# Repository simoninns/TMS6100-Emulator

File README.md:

## Synopsis

TMS6100 speech PHROM (PHrase Read Only Memory) hardware emulator for use with the TMS5220 Voice Synthesis Processor in an Acorn BBC Microcomputer

## Motivation

This project creates a TMS6100 speech PHROM (PHrase Read Only Memory) for use with the TMS5220 Voice Synthesis Processor in an Acorn BBC Microcomputer. Whilst it’s still possible to purchase TMS5220 ICs from sites like Ebay, the TMS6100 was a mask-programmed ROM that Acorn produced specifically for their speech upgrade and is therefore difficult and expensive to source. Instead of using the original ROM, this project uses an ATmega32U2 microcontroller to both emulate the ROM and provide the original Acorn voice sample data recorded by BBC newsreader Kenneth Kendall.

## Installation

Note: This is an Atmel Studio 7 project that can be loaded and compiled by the IDE

Please see http://www.waitingforfriday.com/?p=30 for detailed documentation about TMS6100-Emulator

The PHROM data for both the Acorn Speech System PHROM and the American TI PHROM is included in the source-code.  By default it will compile using the Acorn Speech Data.  Specifying the compiler macro PHROM_ACORN selects the Acorn PHROM and PHROM_US selects the American PHROM.  Note that the American PHROM is not generally for use with the BBC Micro and is included for experimental use (or use in other microcomputer systems).

## Author

TMS6100-Emulator is written and maintained by Simon Inns.

## License (Software)

    TMS6100-Emulator is free software: you can redistribute it and/or modify
    it under the terms of the GNU General Public License as published by
    the Free Software Foundation, either version 3 of the License, or
    (at your option) any later version.

    TMS6100-Emulator is distributed in the hope that it will be useful,
    but WITHOUT ANY WARRANTY; without even the implied warranty of
    MERCHANTABILITY or FITNESS FOR A PARTICULAR PURPOSE.  See the
    GNU General Public License for more details.

    You should have received a copy of the GNU General Public License
    along with TMS6100-Emulator. If not, see <http://www.gnu.org/licenses/>.

## License (Hardware)

Both the schematic and the PCB design of TMS6100-Emulator are covered by a Creative Commons license; as with the software you are welcome (and encouraged!) to extend, re-spin and otherwise use and modify the design as allowed by the license.  However; under the terms of the Attribution-ShareAlike 4.0 International (CC BY-SA 4.0) license you are required to release your design (or redesign) under the same license.  For details of the licensing requirements please see <https://creativecommons.org/licenses/by-sa/4.0/>

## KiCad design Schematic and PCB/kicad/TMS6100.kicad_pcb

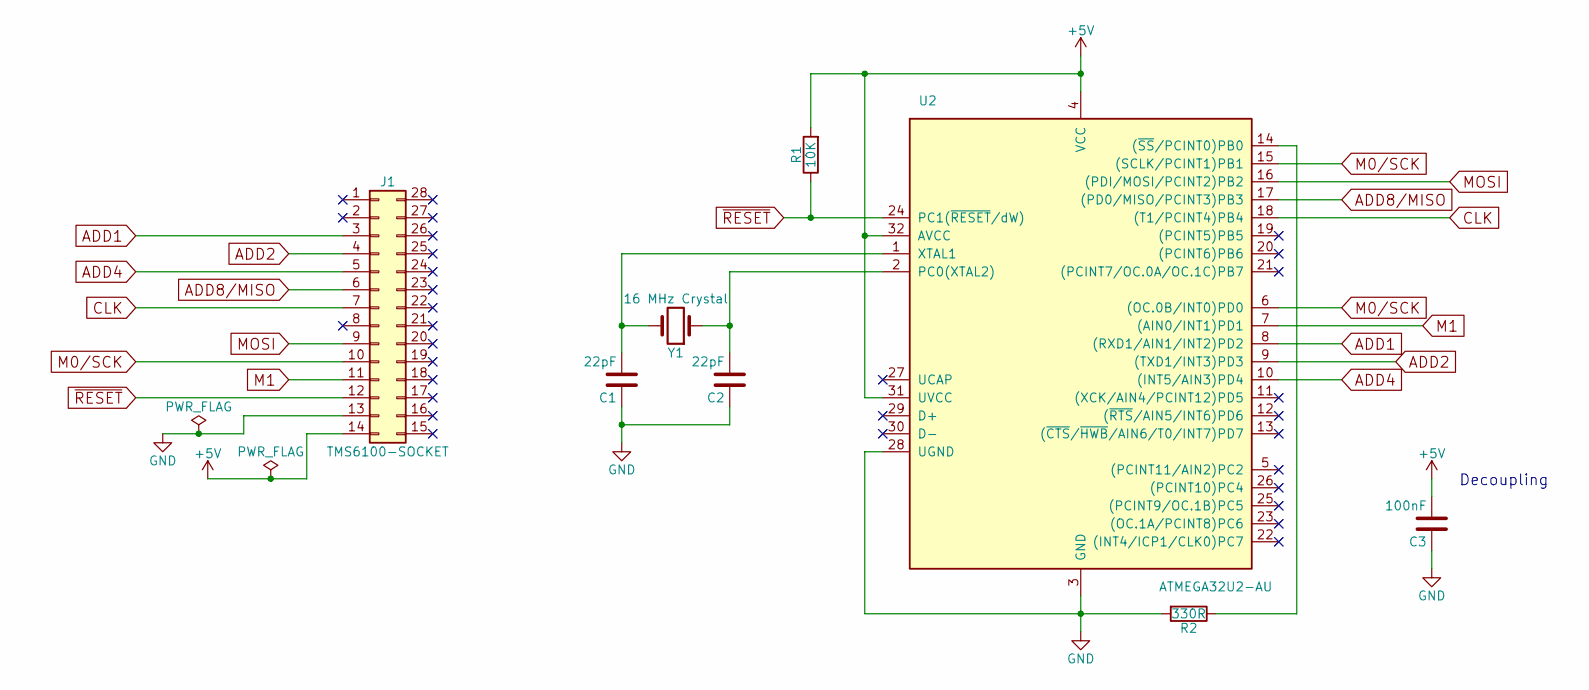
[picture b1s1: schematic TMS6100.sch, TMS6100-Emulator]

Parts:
C1, C2: 22pF; C_0805
C3: 100nF; C_0805
J1: TMS6100-SOCKET; DIP-28_W15.24mm_Socket
R1: 10K; R_0805
R2: 330R; R_0805
U2: ATMEGA32U2-AU; TQFP-32_7x7mm_Pitch0.8mm
Y1: 16 MHz Crystal; Crystal_SMD_5032-2pin_5.0x3.2mm

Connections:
+5V: C3.2, J1.14, R1.2, U2.4 (VCC), U2.31 (UVCC), U2.32 (AVCC)
ADD1: J1.3, U2.8 ((RXD1/AIN1/INT2)PD2)
ADD2: J1.4, U2.9 ((TXD1/INT3)PD3)
ADD4: J1.5, U2.10 ((INT5/AIN3)PD4)
ADD8/MISO: J1.6, U2.17 ((PD0/MISO/PCINT3)PB3)
CLK: J1.7, U2.18 ((T1/PCINT4)PB4)
GND: C1.1, C2.1, C3.1, J1.13, R2.2, U2.3 (GND), U2.28 (UGND)
M0/SCK: J1.10, U2.6 ((OC.0B/INT0)PD0), U2.15 ((SCLK/PCINT1)PB1)
M1: J1.11, U2.7 ((AIN0/INT1)PD1)
MOSI: J1.9, U2.16 ((PDI/MOSI/PCINT2)PB2)
unnamed: C1.2, U2.1 (XTAL1), Y1.2
unnamed: C2.2, U2.2 (PC0(XTAL2)), Y1.1
unnamed: R2.1, U2.14 ((~SS~/PCINT0)PB0)
~RESET: J1.12, R1.1, U2.24 (PC1(~RESET~/dW))

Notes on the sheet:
Decoupling

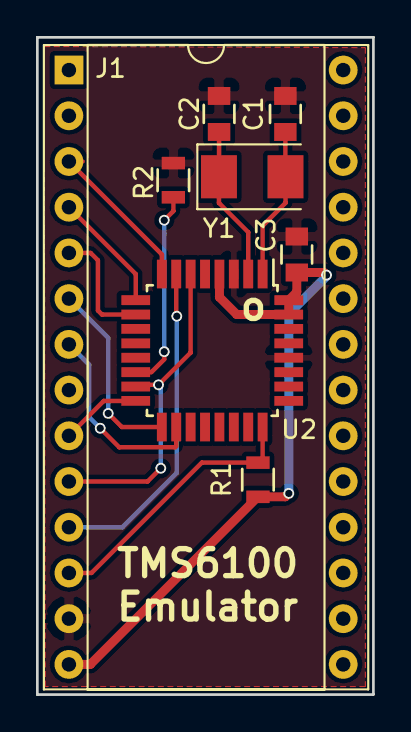
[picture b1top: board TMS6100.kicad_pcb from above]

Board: 2 copper layers, 18.7 x 36.5 mm, 8 parts (0 on the bottom side), 14 nets.

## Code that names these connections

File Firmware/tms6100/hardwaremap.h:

/************************************************************************
	hardwaremap.h

    Physical hardware mapping definitions for portability
    Copyright (C) 2018 Simon Inns

    This file is part of the TMS6100-Emulator.

    The TMS6100-Emulator is free software: you can
    redistribute it and/or modify it under the terms of the GNU
    General Public License as published by the Free Software
    Foundation, either version 3 of the License, or (at your
    option) any later version.

    This program is distributed in the hope that it will be useful,
    but WITHOUT ANY WARRANTY; without even the implied warranty of
    MERCHANTABILITY or FITNESS FOR A PARTICULAR PURPOSE.  See the
    GNU General Public License for more details.

    You should have received a copy of the GNU General Public License
    along with this program.  If not, see <http://www.gnu.org/licenses/>.

    Email: simon.inns@gmail.com

    ************************************************************************/

#ifndef HARDWAREMAP_H_
#define HARDWAREMAP_H_

// Target device: ATmega32u2
// Also tested on the ATmega32u4 (Arduino Leonardo mini pro)

// Definitions for TMS6100 IO Pins --------------------------------------

// ADD1 (PD2)
#define TMS6100_ADD1_PORT	PORTD
#define TMS6100_ADD1_PIN	PIND
#define TMS6100_ADD1_DDR	DDRD
#define TMS6100_ADD1		(1 << 2)

// ADD2 (PD3)
#define TMS6100_ADD2_PORT	PORTD
#define TMS6100_ADD2_PIN	PIND
#define TMS6100_ADD2_DDR	DDRD
#define TMS6100_ADD2		(1 << 3)

// ADD4 (PD4)
#define TMS6100_ADD4_PORT	PORTD
#define TMS6100_ADD4_PIN	PIND
#define TMS6100_ADD4_DDR	DDRD
#define TMS6100_ADD4		(1 << 4)

// ADD8 (PB3/MOSI)
#define TMS6100_ADD8_PORT	PORTB
#define TMS6100_ADD8_PIN	PINB
#define TMS6100_ADD8_DDR	DDRB
#define TMS6100_ADD8		(1 << 3)

// M0 (PD0/INT0)
#define TMS6100_M0_PORT		PORTD
#define TMS6100_M0_PIN		PIND
#define TMS6100_M0_DDR		DDRD
#define TMS6100_M0			(1 << 0)
#define TMS6100_M0_INT		INT0
#define TMS6100_M0_INT_VECT	INT0_vect
#define TMS6100_M0_ISC0		ISC00
#define TMS6100_M0_ISC1		ISC01
#define TMS6100_M0_INTF		INTF0

// M1 (PD1/INT1)
#define TMS6100_M1_PORT		PORTD
#define TMS6100_M1_PIN		PIND
#define TMS6100_M1_DDR		DDRD
#define TMS6100_M1			(1 << 1)
#define TMS6100_M1_INT		INT1
#define TMS6100_M1_INT_VECT	INT1_vect
#define TMS6100_M1_ISC0		ISC10
#define TMS6100_M1_ISC1		ISC11
#define TMS6100_M1_INTF		INTF1

// CLK (PB4) - Not currently used by the emulator as we use
// the SPI module to asynchronously time data based on the 
// M0 pulses (which has the effect of making the data in sync
// with the clock).
#define TMS6100_CLK_PORT	PORTB
#define TMS6100_CLK_PIN		PINB
#define TMS6100_CLK_DDR		DDRB
#define TMS6100_CLK			(1 << 4)

// Definitions for SPI pins ---------------------------------------------

// MISO - This is ADD8 defined above 

// MOSI (PB2)
#define TMS6100_MOSI_PORT	PORTB
#define TMS6100_MOSI_PIN	PINB
#define TMS6100_MOSI_DDR	DDRB
#define TMS6100_MOSI		(1 << 2)

// SCK (PB1)
#define TMS6100_SCK_PORT	PORTB
#define TMS6100_SCK_PIN		PINB
#define TMS6100_SCK_DDR		DDRB
#define TMS6100_SCK			(1 << 1)

// !SS (PB0)
#define TMS6100_SS_PORT		PORTB
#define TMS6100_SS_PIN		PINB
#define TMS6100_SS_DDR		DDRB
#define TMS6100_SS			(1 << 0)

// Definitions for debug pins -------------------------------------------

// Note: These pins are used for development and are not present
// on the production version of the PCB

#define DEBUG0_PORT	PORTD
#define DEBUG0_PIN	PIND
#define DEBUG0_DDR	DDRD
#define DEBUG0		(1 << 5)

#define DEBUG1_PORT	PORTD
#define DEBUG1_PIN	PIND
#define DEBUG1_DDR	DDRD
#define DEBUG1		(1 << 6)

#define DEBUG2_PORT	PORTD
#define DEBUG2_PIN	PIND
#define DEBUG2_DDR	DDRD
#define DEBUG2		(1 << 7)

#endif /* HARDWAREMAP_H_ */

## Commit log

2018-04-10 Initial commit of project files (firmware and eagle cad)
2018-04-10 Corrected source files - fixed header information
2018-04-10 kicad schematics
2018-04-10 Updated schematic and included fixes
    I've modified the labels into global labels and corrected PB0. Components and nodes have been space out to make the diagram clearer. Power connections are now pointing in the correct directions. Also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
2018-04-12 Fix ERC, also socket
2018-04-12 Correct component for socket, footprints mapped
2018-04-14 V1 PCB Layout
2018-04-14 Silkscreen fixed
2018-04-14 Vias fixed
2018-04-14 reverse ground plane added
2018-04-15 Additional changes to schematic and PCB
    Added 'R' to 330R resistor
    Added PCB edge cuts and rearranged text markers into boundaries
    Orientated resistors the same for quicker assembly
    Added URL for WFF
    Added additional marker for TQPF visual orientation
    Removed unnecessary vias around reset pull up resistor
2018-04-15 Added gerbers and PDF files, removed Eagle files
2018-05-01 Added CC license to KiCAD files
2018-05-07 Fixed issue where fuse setting prevented emulator from functioning
    Added override for WDT and clock div 8 fuse settings (now works with stock ATmega32u2 without the need to reprogram fuses).
    Also fixed build environment to compile in release mode rather than debug (with -O1 optimisation).
2018-05-10 Added American PHROM speech data and compiler directives to select required image.
    Specifying -DPHROM_ACORN will compile the Acorn Speech System PHROM data (default) and specifying -DPHROM_US will compile the US speech PHROM data.
2018-06-15 Added support for PHROM bank number
    The emulator now honours the PHROM bank number meaning that, on a BBC Micro SOUND -1, x, 0, 0 will address the Acorn PHROM and SOUND -16, x, 0, 0 will access the US PHROM. Address incrementation has 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
    Note that 'stacking' of PHROMs will not currenly work as the emulator's pins are not passive when another bank is selected.
2018-06-17 Removed SPI, replaced with bit-banging method
    The use of the SPI module has been removed to allow better control over the READ DATA command signals. The READ DATA command is now performed purely using interrupts on the M0 signal.
2018-06-17 Added code to float ADD8 when PHROM's bank isn't selected. Code currently shows timing issues
    READ DATA command is not currently 100% successful. Emulator is causing sample corruption.
2018-06-17 Removed Interrupt Service Requests to improve response speeds
2018-06-17 Non-functioning build - access time from M0 control still to slow (needs to be <2us)
2018-06-17 Revert "Non-functioning build - access time from M0 control still to slow (needs to be <2us)"
    This reverts commit 3a050840b85f405825ca27e36f8b6f29d2051f4c.
2018-06-17 Added back in SPI code - timing of data output on ADD8 is not correct
    The timing possible without using SPI is not fast enough for the primary transfer. Remerging SPI code. Idea will be to use SPI when bank is valid and then use interrupts to track M0 during non-local 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
2018-06-18 Interim check in with SPI re-enabled
    Not currently working; first read data is missing a leading 0
2018-06-23 Better logic trace comparison to original PHROM, but still non-functional
2018-06-28 New working version without interrupts or SPI - with more accurate timing
2018-06-28 Emulator now correctly supports 'stacked' PHROMs allowing multiple PHROMs to be used at once
2018-06-29 Minor clean-up of code

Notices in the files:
Schematic and PCB/kicad/TMS6100.kicad_pcb:
License: Attribution-ShareAlike 4.0 International (CC BY-SA 4.0)
(c) 2018 Simon Inns and Daniel Jameson
(c) 2018 Simon Inns, Daniel Jameson
